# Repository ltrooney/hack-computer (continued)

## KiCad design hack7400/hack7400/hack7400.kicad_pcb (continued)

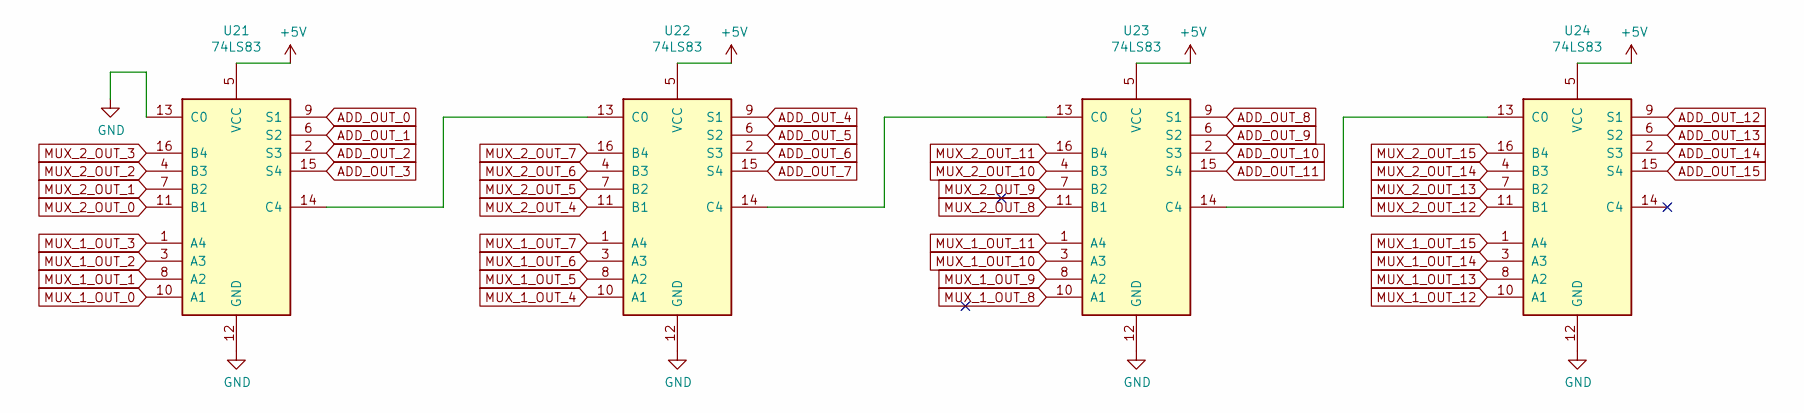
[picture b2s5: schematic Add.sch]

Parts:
U21, U22, U23, U24: 74LS83; DIP-16_W7.62mm_Socket

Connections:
+5V: U21.5 (VCC), U22.5 (VCC), U23.5 (VCC), U24.5 (VCC); also elsewhere on the board
ADD_OUT_0: U21.9 (S1); also elsewhere on the board
ADD_OUT_1: U21.6 (S2); also elsewhere on the board
ADD_OUT_2: U21.2 (S3); also elsewhere on the board
ADD_OUT_3: U21.15 (S4); also elsewhere on the board
ADD_OUT_4: U22.9 (S1); also elsewhere on the board
ADD_OUT_5: U22.6 (S2); also elsewhere on the board
ADD_OUT_6: U22.2 (S3); also elsewhere on the board
ADD_OUT_7: U22.15 (S4); also elsewhere on the board
ADD_OUT_8: U23.9 (S1); also elsewhere on the board
ADD_OUT_9: U23.6 (S2); also elsewhere on the board
ADD_OUT_10: U23.2 (S3); also elsewhere on the board
ADD_OUT_11: U23.15 (S4); also elsewhere on the board
ADD_OUT_12: U24.9 (S1); also elsewhere on the board
ADD_OUT_13: U24.6 (S2); also elsewhere on the board
ADD_OUT_14: U24.2 (S3); also elsewhere on the board
ADD_OUT_15: U24.15 (S4); also elsewhere on the board
GND: U21.12 (GND), U21.13 (C0), U22.12 (GND), U23.12 (GND), U24.12 (GND); also elsewhere on the board
MUX_1_OUT_0: U21.10 (A1); also elsewhere on the board
MUX_1_OUT_1: U21.8 (A2); also elsewhere on the board
MUX_1_OUT_2: U21.3 (A3); also elsewhere on the board
MUX_1_OUT_3: U21.1 (A4); also elsewhere on the board
MUX_1_OUT_4: U22.10 (A1); also elsewhere on the board
MUX_1_OUT_5: U22.8 (A2); also elsewhere on the board
MUX_1_OUT_6: U22.3 (A3); also elsewhere on the board
MUX_1_OUT_7: U22.1 (A4); also elsewhere on the board
MUX_1_OUT_8: U23.10 (A1); also elsewhere on the board
MUX_1_OUT_9: U23.8 (A2); also elsewhere on the board
MUX_1_OUT_10: U23.3 (A3); also elsewhere on the board
MUX_1_OUT_11: U23.1 (A4); also elsewhere on the board
MUX_1_OUT_12: U24.10 (A1); also elsewhere on the board
MUX_1_OUT_13: U24.8 (A2); also elsewhere on the board
MUX_1_OUT_14: U24.3 (A3); also elsewhere on the board
MUX_1_OUT_15: U24.1 (A4); also elsewhere on the board
MUX_2_OUT_0: U21.11 (B1); also elsewhere on the board
MUX_2_OUT_1: U21.7 (B2); also elsewhere on the board
MUX_2_OUT_2: U21.4 (B3); also elsewhere on the board
MUX_2_OUT_3: U21.16 (B4); also elsewhere on the board
MUX_2_OUT_4: U22.11 (B1); also elsewhere on the board
MUX_2_OUT_5: U22.7 (B2); also elsewhere on the board
MUX_2_OUT_6: U22.4 (B3); also elsewhere on the board
MUX_2_OUT_7: U22.16 (B4); also elsewhere on the board
MUX_2_OUT_8: U23.11 (B1); also elsewhere on the board
MUX_2_OUT_9: U23.7 (B2); also elsewhere on the board
MUX_2_OUT_10: U23.4 (B3); also elsewhere on the board
MUX_2_OUT_11: U23.16 (B4); also elsewhere on the board
MUX_2_OUT_12: U24.11 (B1); also elsewhere on the board
MUX_2_OUT_13: U24.7 (B2); also elsewhere on the board
MUX_2_OUT_14: U24.4 (B3); also elsewhere on the board
MUX_2_OUT_15: U24.16 (B4); also elsewhere on the board
unnamed: U21.14 (C4), U22.13 (C0)
unnamed: U22.14 (C4), U23.13 (C0)
unnamed: U23.14 (C4), U24.13 (C0)

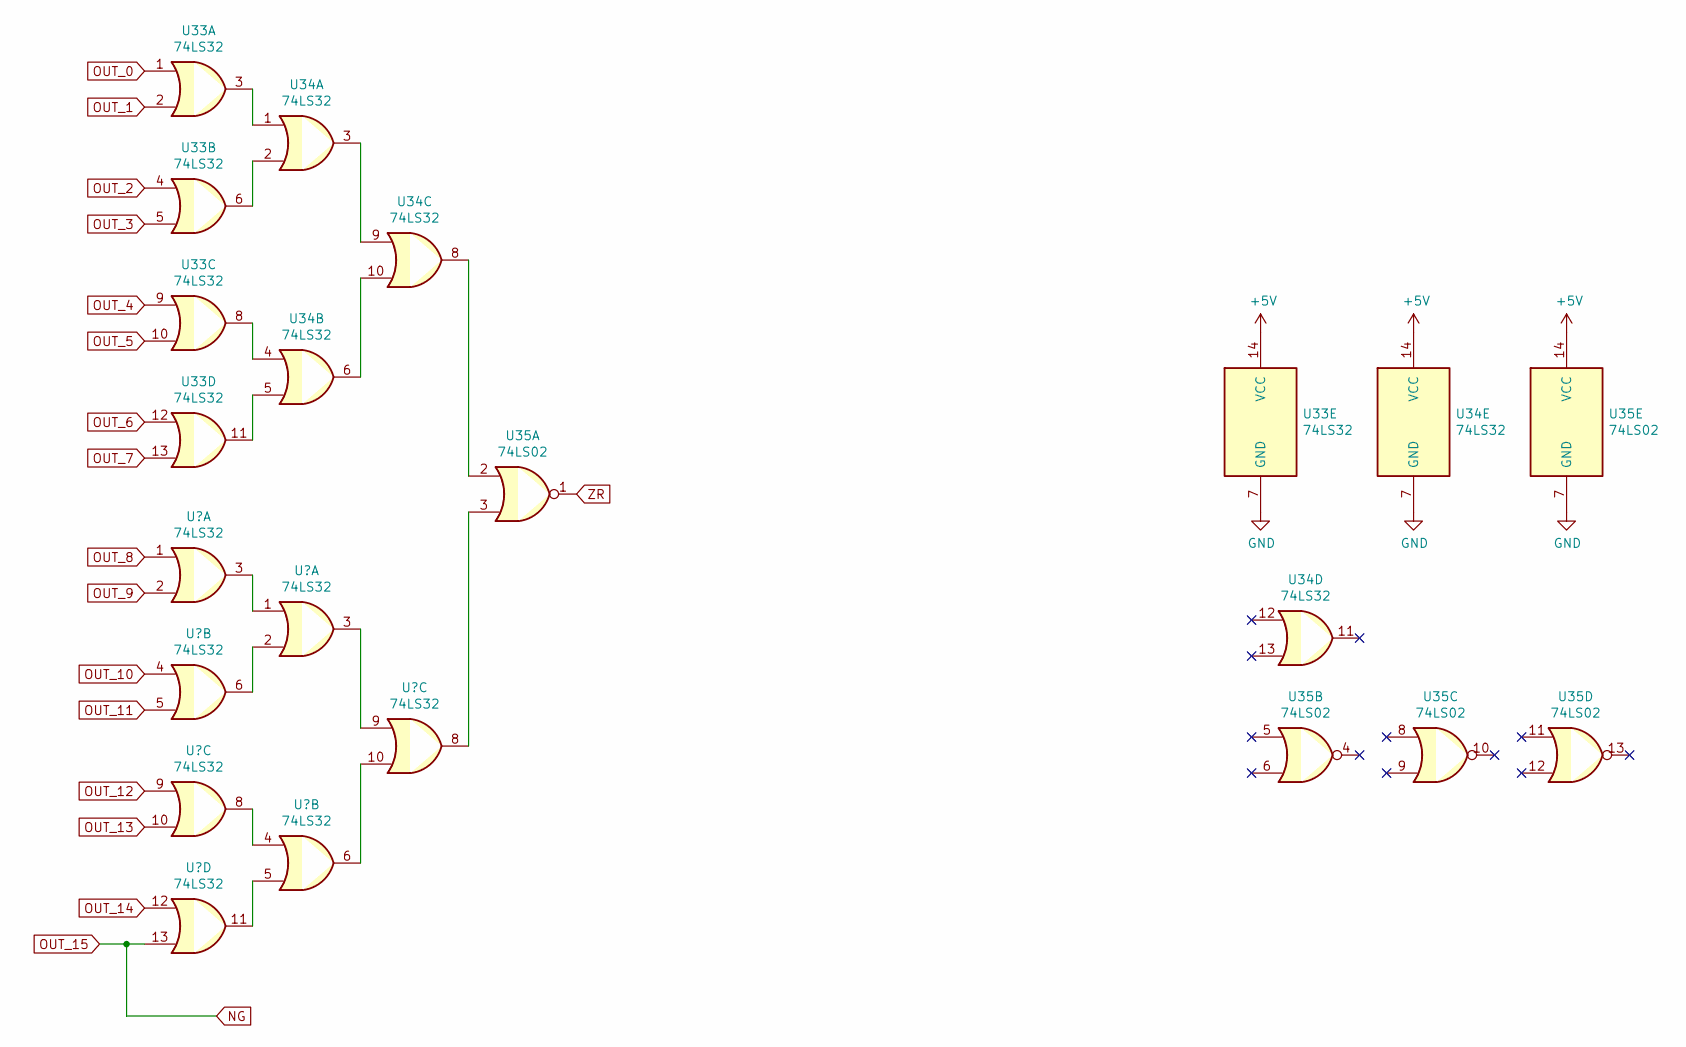
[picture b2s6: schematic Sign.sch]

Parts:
U33, U34: 74LS32
U35: 74LS02

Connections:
+5V: U33.14 (VCC), U34.14 (VCC), U35.14 (VCC); also elsewhere on the board
GND: U33.7 (GND), U34.7 (GND), U35.7 (GND); also elsewhere on the board
unnamed: U33.3, U34.1
unnamed: U33.6, U34.2
unnamed: U33.8, U34.4
unnamed: U33.11, U34.5
unnamed: U34.3, U34.9
unnamed: U34.8, U35.2
unnamed: U34.6, U34.10
unnamed 189: U35.3; also elsewhere on the board
OUT_0: U33.1; also elsewhere on the board
OUT_1: U33.2; also elsewhere on the board
OUT_2: U33.4; also elsewhere on the board
OUT_3: U33.5; also elsewhere on the board
OUT_4: U33.9; also elsewhere on the board
OUT_5: U33.10; also elsewhere on the board
OUT_6: U33.12; also elsewhere on the board
OUT_7: U33.13; also elsewhere on the board
ZR: U35.1; also elsewhere on the board

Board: 2 copper layers, 155 parts (1 on the bottom side), 242 nets, no tracks yet.

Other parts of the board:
U25, U26, U27, U28: 74LS157; DIP-16_W7.62mm_Socket
U29, U30, U31, U32: 74LS86; DIP-14_W7.62mm_Socket
U36, U37: 74LS32; DIP-14_W7.62mm_Socket

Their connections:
+5V: U25.16, U26.16, U27.16, U28.16, U29.14, U30.14, U31.14, U32.14; also elsewhere on the board
ADD_OUT_0: U25.2; also elsewhere on the board
ADD_OUT_1: U25.5; also elsewhere on the board
ADD_OUT_2: U25.11; also elsewhere on the board
ADD_OUT_3: U25.14; also elsewhere on the board
ADD_OUT_4: U26.2; also elsewhere on the board
ADD_OUT_5: U26.5; also elsewhere on the board
ADD_OUT_6: U26.11; also elsewhere on the board
ADD_OUT_7: U26.14; also elsewhere on the board
ADD_OUT_8: U27.2; also elsewhere on the board
ADD_OUT_9: U27.5; also elsewhere on the board
ADD_OUT_10: U27.11; also elsewhere on the board
ADD_OUT_11: U27.14; also elsewhere on the board
ADD_OUT_12: U28.2; also elsewhere on the board
ADD_OUT_13: U28.5; also elsewhere on the board
ADD_OUT_14: U28.11; also elsewhere on the board
ADD_OUT_15: U28.14; also elsewhere on the board
AND_OUT_0: U25.3; also elsewhere on the board
AND_OUT_1: U25.6; also elsewhere on the board
AND_OUT_2: U25.10; also elsewhere on the board
AND_OUT_3: U25.13; also elsewhere on the board
AND_OUT_4: U26.3; also elsewhere on the board
AND_OUT_5: U26.6; also elsewhere on the board
AND_OUT_6: U26.10; also elsewhere on the board
AND_OUT_7: U26.13; also elsewhere on the board
AND_OUT_8: U27.3; also elsewhere on the board
AND_OUT_9: U27.6; also elsewhere on the board
AND_OUT_10: U27.10; also elsewhere on the board
AND_OUT_11: U27.13; also elsewhere on the board
AND_OUT_12: U28.3; also elsewhere on the board
AND_OUT_13: U28.6; also elsewhere on the board
AND_OUT_14: U28.10; also elsewhere on the board
AND_OUT_15: U28.13; also elsewhere on the board
F: U25.1, U26.1, U27.1, U28.1; also elsewhere on the board
GND: U25.8, U25.15, U26.8, U26.15, U27.8, U27.15, U28.8, U28.15, U29.7, U30.7, U31.7, U32.7; also elsewhere on the board
NG: U32.11, U36.13; also elsewhere on the board
NO: U29.2, U29.5, U29.10, U29.13, U30.2, U30.5, U30.10, U30.13, U31.2, U31.5, U31.10, U31.13, U32.2, U32.5, U32.10, U32.13; also elsewhere on the board
unnamed: U25.4, U29.1
unnamed: U25.7, U29.4
unnamed: U25.9, U29.9
unnamed: U25.12, U29.12
unnamed: U26.4, U30.1
unnamed: U26.7, U30.4
unnamed: U26.9, U30.9
unnamed: U26.12, U30.12
unnamed: U27.4, U31.1
unnamed: U27.7, U31.4
unnamed: U27.9, U31.9
unnamed: U27.12, U31.12
unnamed: U28.4, U32.1
unnamed: U28.7, U32.4
unnamed: U28.9, U32.9
unnamed: U28.12, U32.12
unnamed 189: U37.8; also elsewhere on the board
unnamed: U36.3, U37.1
unnamed: U36.6, U37.2
unnamed: U36.8, U37.4
unnamed: U36.11, U37.5
unnamed: U37.3, U37.9
unnamed: U37.6, U37.10
OUT_0: U29.3; also elsewhere on the board
OUT_1: U29.6; also elsewhere on the board
OUT_2: U29.8; also elsewhere on the board
OUT_3: U29.11; also elsewhere on the board
OUT_4: U30.3; also elsewhere on the board
OUT_5: U30.6; also elsewhere on the board
OUT_6: U30.8; also elsewhere on the board
OUT_7: U30.11; also elsewhere on the board
OUT_8: U31.3, U36.1; also elsewhere on the board
OUT_9: U31.6, U36.2; also elsewhere on the board
OUT_10: U31.8, U36.4; also elsewhere on the board
OUT_11: U31.11, U36.5; also elsewhere on the board
OUT_12: U32.3, U36.9; also elsewhere on the board
OUT_13: U32.6, U36.10; also elsewhere on the board
OUT_14: U32.8, U36.12; also elsewhere on the board

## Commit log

2019-08-27 initial commit of files, including full computer implementation
2020-05-22 Added Logisim CPU file
2020-05-23 Updated top level CPU circuit
2020-05-23 Added 7400 version of the Hack computer Logisim simulation
2020-05-24 Fixed bugs in CPU circuits and added external libraries
2020-05-24 Updated memory to 2 banks each consisting of 8 of 2K x 8 bit RAM
2020-05-24 Created schematic in KiCad
2020-05-25 Updated schematic
2020-05-25 Started layout process
2020-05-25 Added 4-bit version of the schematic and started layout process
2020-05-26 finished PCB layout
